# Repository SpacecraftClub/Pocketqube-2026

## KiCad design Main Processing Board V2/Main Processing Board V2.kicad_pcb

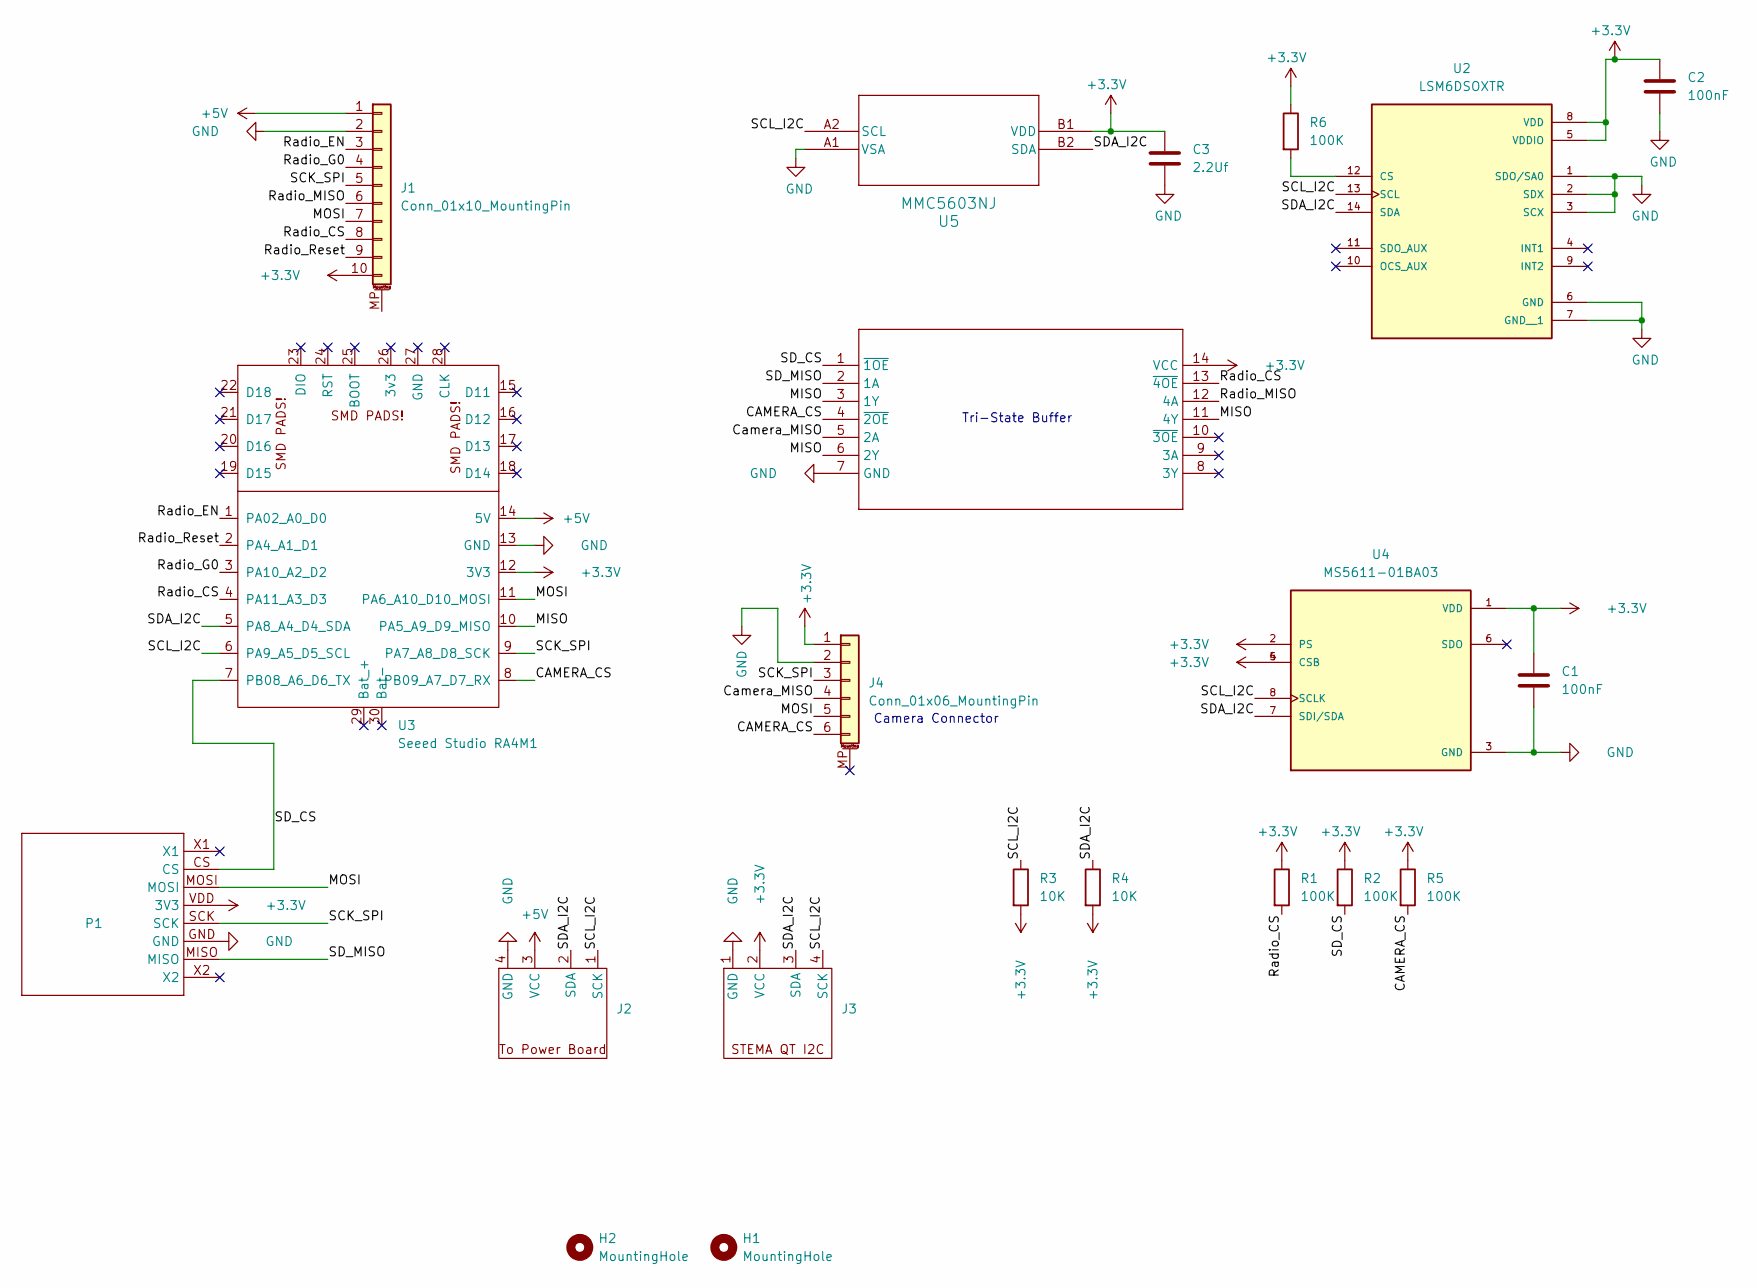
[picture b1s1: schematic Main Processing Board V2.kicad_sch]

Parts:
C1, C2: 100nF; C_1206_3216Metric_Pad1.33x1.80mm_HandSolder
C3: 2.2Uf; C_0603_1608Metric_Pad1.08x0.95mm_HandSolder
H1, H2: MountingHole; MountingHole_2.2mm_M2
J1: Conn_01x10_MountingPin; JST_SH_BM10B-SRSS-TB_1x10-1MP_P1.00mm_Vertical
J2, J3: JST_SH_BM04B-SRSS-TB_1x04-1MP_P1.00mm_Vertical
J4: Conn_01x06_MountingPin; JST_SH_BM06B-SRSS-TB_1x06-1MP_P1.00mm_Vertical
P1: SDREAD
R1, R2, R5, R6: 100K; R_0603_1608Metric_Pad0.98x0.95mm_HandSolder
R3, R4: 10K; R_0805_2012Metric_Pad1.20x1.40mm_HandSolder
U1: NS14
U2: LSM6DSOXTR; 14-VFLGA; PARTREV 3.0
U3: Seeed Studio RA4M1; XIAO-RA4M1-SMD
U4: MS5611-01BA03; SON125P500X300X100-8N; PARTREV 06/2017
U5: MMC5603NJ; WLP4_0P82X0P82_MEM

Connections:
+3.3V: C1.1, C2.1, C3.1, J1.10, J3.2 (VCC), J4.1, P1.VDD (3V3), R1.1, R2.1, R3.2, R4.2, R5.1, R6.1, U1.14 (VCC), U2.5 (VDDIO), U2.8 (VDD), U3.12 (3V3), U4.1 (VDD), U4.2 (PS), U4.4 (CSB), U4.5 (CSB), U5.B1 (VDD)
+5V: J1.1, J2.3 (VCC), U3.14 (5V)
/CAMERA_CS: J4.6, R5.2, U1.4 (~2OE), U3.8 (PB09_A7_D7_RX)
/Camera_MISO: J4.4, U1.5 (2A)
/MISO: U1.3 (1Y), U1.6 (2Y), U1.11 (4Y), U3.10 (PA5_A9_D9_MISO)
/MOSI: J1.7, J4.5, P1.MOSI, U3.11 (PA6_A10_D10_MOSI)
/Radio_CS: J1.8, R1.2, U1.13 (~4OE), U3.4 (PA11_A3_D3)
/Radio_EN: J1.3, U3.1 (PA02_A0_D0)
/Radio_G0: J1.4, U3.3 (PA10_A2_D2)
/Radio_MISO: J1.6, U1.12 (4A)
/Radio_Reset: J1.9, U3.2 (PA4_A1_D1)
/SCK_SPI: J1.5, J4.3, P1.SCK, U3.9 (PA7_A8_D8_SCK)
/SCL_I2C: J2.1 (SCK), J3.4 (SCK), R3.1, U2.13 (SCL), U3.6 (PA9_A5_D5_SCL), U4.8 (SCLK), U5.A2 (SCL)
/SDA_I2C: J2.2 (SDA), J3.3 (SDA), R4.1, U2.14 (SDA), U3.5 (PA8_A4_D4_SDA), U4.7 (SDI/SDA), U5.B2 (SDA)
/SD_CS: P1.CS, R2.2, U1.1 (~1OE), U3.7 (PB08_A6_D6_TX)
/SD_MISO: P1.MISO, U1.2 (1A)
GND: C1.2, C2.2, C3.2, J1.2, J2.4 (GND), J3.1 (GND), J4.2, P1.GND, U1.7 (GND), U2.1 (SDO/SA0), U2.2 (SDX), U2.3 (SCX), U2.6 (GND), U2.7 (GND__1), U3.13 (GND), U4.3 (GND), U5.A1 (VSA)
unnamed: R6.2, U2.12 (CS)

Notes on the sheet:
Camera Connector
Tri-State Buffer

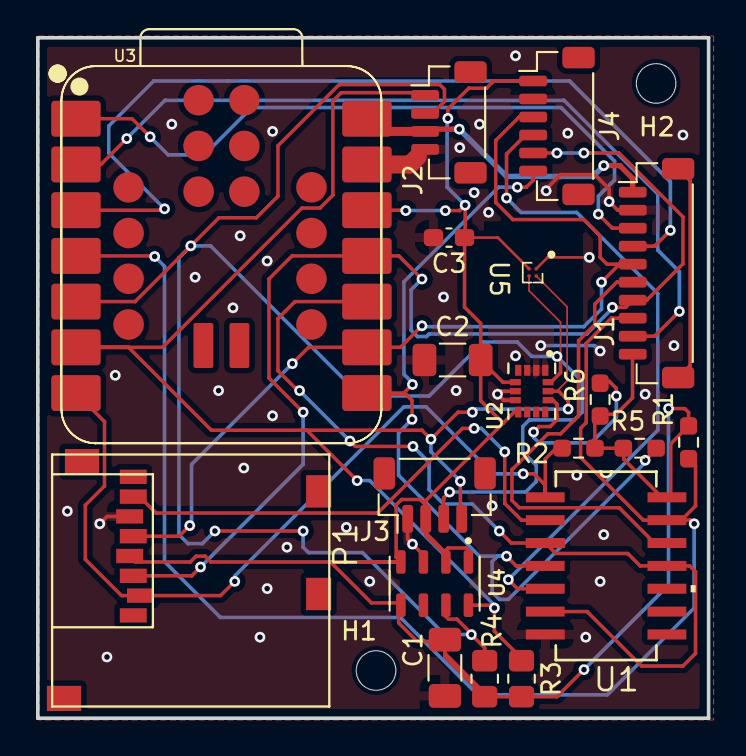
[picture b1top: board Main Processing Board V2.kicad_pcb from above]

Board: 2 copper layers, 37.3 x 37.8 mm, 21 parts (0 on the bottom side), 18 nets.

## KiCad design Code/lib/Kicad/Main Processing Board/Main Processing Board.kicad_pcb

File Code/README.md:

# PocketQube Flight Code

This firmware collects sensor data, logs it to the SD card, and transmits telemetry over LoRa radio.

## Viewing Data

There are three output paths:

1. Serial monitor
   Set `PRINT_SENSOR_CSV` to `true` in `src/main.cpp`. The firmware will print one CSV row per second at `9600` baud.

2. SD card logs
   Sensor data is written to CSV files by `src/sensor_logger.cpp`. Each row contains the current exported values for every sensor task.

3. Radio telemetry
   `src/radio.cpp` sends a binary packet containing a 2-byte sequence number followed by all exported sensor floats in task order.

## Sensor Task Order

Radio telemetry and CSV column order both follow the `sensorTasks[]` array in `src/taskHandles.cpp`.

Current task order:

1. `MS5611_Task`
2. `MMC5603_Task`
3. `LMSModule_Task`
4. `DS2782_BatteryMonitor_Task` when `POWER_MONITOR` is enabled

## Telemetry Field Order

### Base 12-float telemetry layout

If the battery monitor is not included in the radio payload, the 12 floats are:

1. `Pressure`
2. `Temp (MS5611)`
3. `x_mag`
4. `y_mag`
5. `z_mag`
6. `accel_x`
7. `accel_y`
8. `accel_z`
9. `gyro_x`
10. `gyro_y`
11. `gyro_z`
12. `temp_LMS`

Example:

`Telemetry: SEQ=9 Floats(12): 84966.555 23.303 913.164 1053.115 592.743 -0.002 0.120 1.024 -0.366 0.149 -0.549 20.222`

This maps to:

1. `84966.555` = `Pressure`
2. `23.303` = `Temp (MS5611)`
3. `913.164` = `x_mag`
4. `1053.115` = `y_mag`
5. `592.743` = `z_mag`
6. `-0.002` = `accel_x`
7. `0.120` = `accel_y`
8. `1.024` = `accel_z`
9. `-0.366` = `gyro_x`
10. `0.149` = `gyro_y`
11. `-0.549` = `gyro_z`
12. `20.222` = `temp_LMS`

### Battery monitor fields

When `POWER_MONITOR` is enabled, the DS2782 task adds these fields after `temp_LMS`:

13. `batt_voltage`
14. `batt_current`
15. `batt_power`
16. `batt_energy`
17. `batt_capacity`
18. `batt_soc`

## Likely Units

1. `Pressure`: Pa
2. `Temp (MS5611)`: C
3. `x_mag`, `y_mag`, `z_mag`: uT
4. `accel_x`, `accel_y`, `accel_z`: g
5. `gyro_x`, `gyro_y`, `gyro_z`: deg/s
6. `temp_LMS`: C
7. `batt_voltage`: V
8. `batt_current`: A
9. `batt_power`: W
10. `batt_energy`: J
11. `batt_capacity`: mAh
12. `batt_soc`: percent

## Important Radio Note

`src/radio.cpp` now computes the telemetry payload length from the enabled sensor tasks and checks it against `MAX_TELEMETRY_PACKET_LEN = 96`.

That is enough for the current telemetry set:

1. `2` bytes of sequence number
2. `18` floats = `72` bytes
3. Total `74` bytes

If more sensor fields are added later and the payload grows past `96` bytes, radio initialization will fail until the limit is increased.

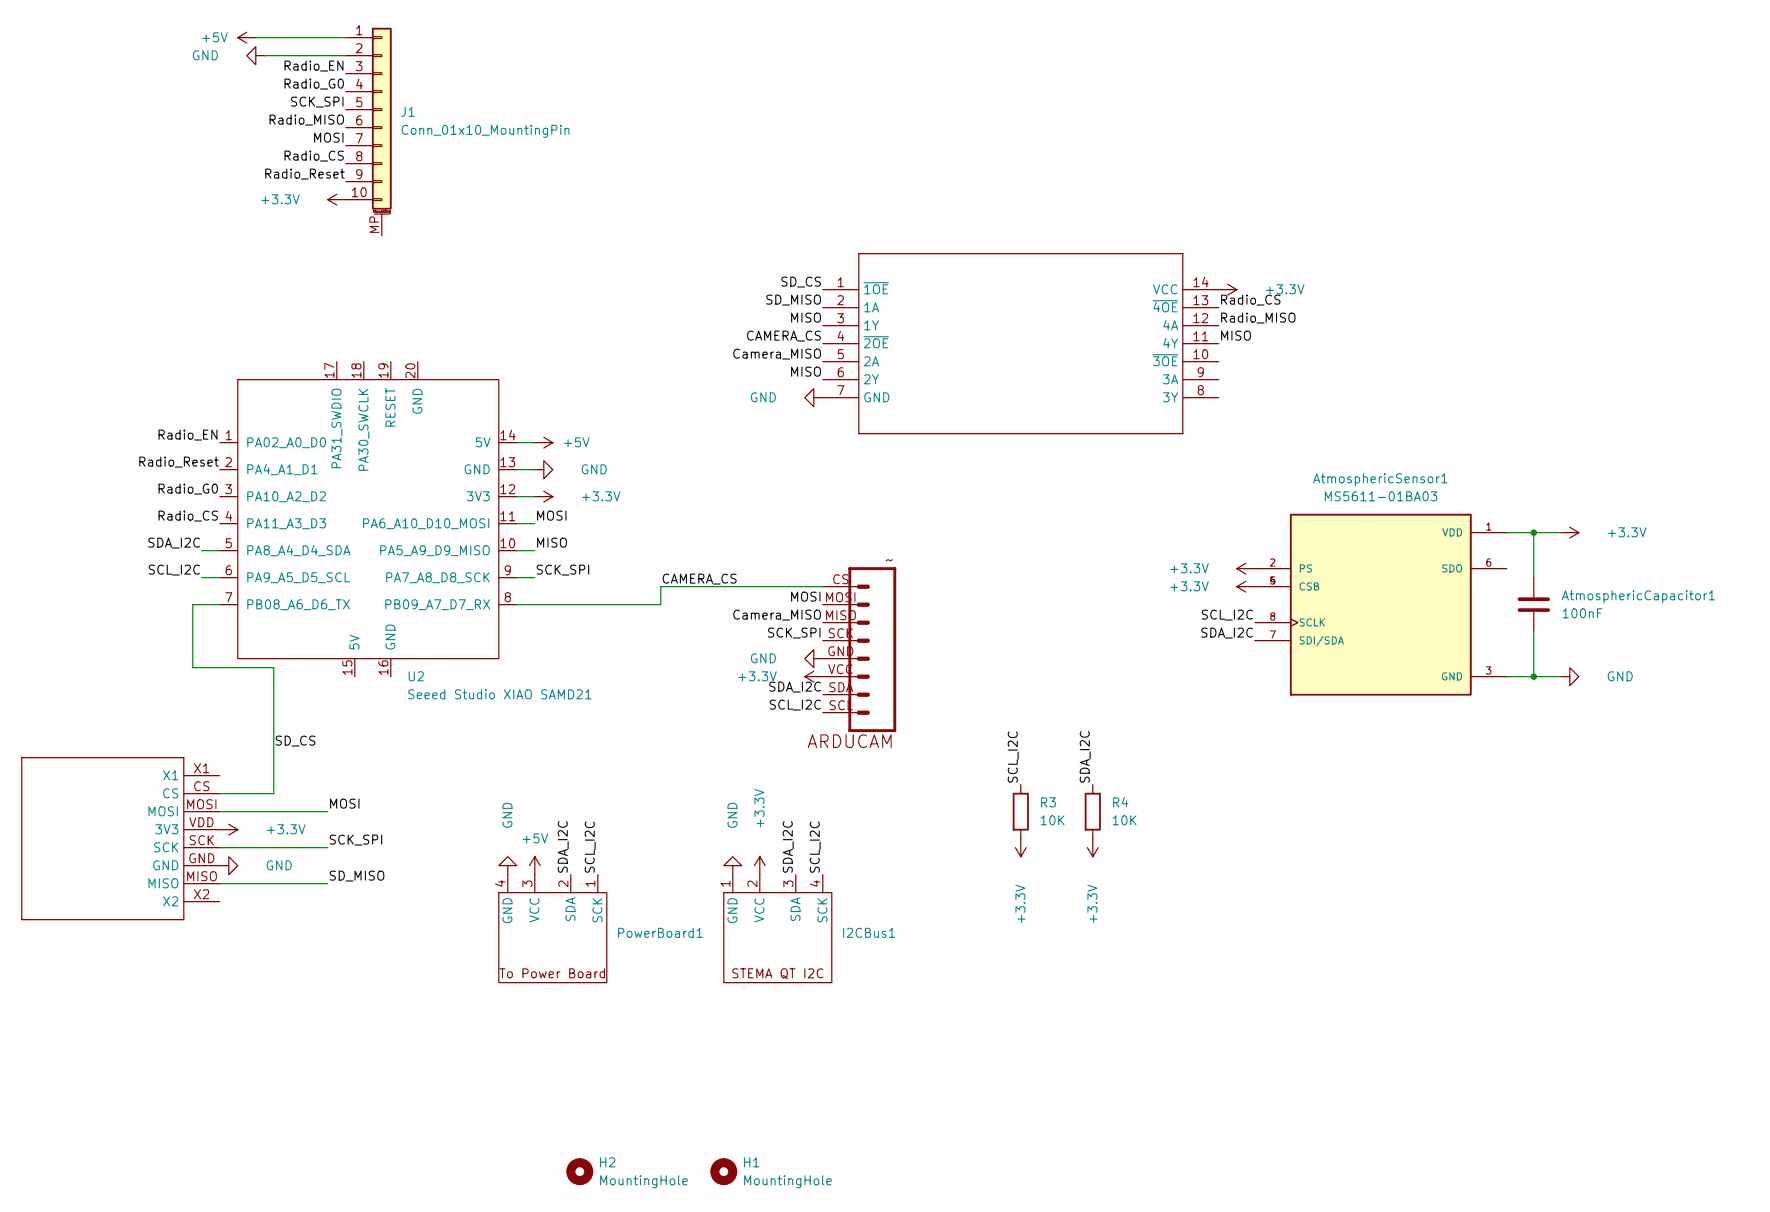
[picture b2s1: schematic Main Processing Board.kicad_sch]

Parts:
11111: SDREAD
12111: ARDUCAM_MINI
AtmosphericCapacitor1: 100nF; C_1206_3216Metric_Pad1.33x1.80mm_HandSolder
AtmosphericSensor1: MS5611-01BA03; SON125P500X300X100-8N; PARTREV 06/2017
H1, H2: MountingHole; MountingHole_2.2mm_M2
I2CBus1: JST_SH_BM04B-SRSS-TB_1x04-1MP_P1.00mm_Vertical
J1: Conn_01x10_MountingPin; JST_SH_BM10B-SRSS-TB_1x10-1MP_P1.00mm_Vertical
PowerBoard1: Molex_PicoBlade_53047-0410_1x04_P1.25mm_Vertical
R3, R4: 10K; R_0805_2012Metric_Pad1.20x1.40mm_HandSolder
U1: NS14
U2: Seeed Studio XIAO SAMD21; XIAO-SAMD21-SMD

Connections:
+3.3V: 11111.VDD (3V3), 12111.VCC, AtmosphericCapacitor1.1, AtmosphericSensor1.1 (VDD), AtmosphericSensor1.2 (PS), AtmosphericSensor1.4 (CSB), AtmosphericSensor1.5 (CSB), I2CBus1.2 (VCC), J1.10, R3.2, R4.2, U1.14 (VCC), U2.12 (3V3)
+5V: J1.1, PowerBoard1.3 (VCC), U2.14 (5V)
/CAMERA_CS: 12111.CS, U1.4 (~2OE), U2.8 (PB09_A7_D7_RX)
/Camera_MISO: 12111.MISO, U1.5 (2A)
/MISO: U1.3 (1Y), U1.6 (2Y), U1.11 (4Y), U2.10 (PA5_A9_D9_MISO)
/MOSI: 11111.MOSI, 12111.MOSI, J1.7, U2.11 (PA6_A10_D10_MOSI)
/Radio_CS: J1.8, U1.13 (~4OE), U2.4 (PA11_A3_D3)
/Radio_EN: J1.3, U2.1 (PA02_A0_D0)
/Radio_G0: J1.4, U2.3 (PA10_A2_D2)
/Radio_MISO: J1.6, U1.12 (4A)
/Radio_Reset: J1.9, U2.2 (PA4_A1_D1)
/SCK_SPI: 11111.SCK, 12111.SCK, J1.5, U2.9 (PA7_A8_D8_SCK)
/SCL_I2C: 12111.SCL, AtmosphericSensor1.8 (SCLK), I2CBus1.4 (SCK), PowerBoard1.1 (SCK), R3.1, U2.6 (PA9_A5_D5_SCL)
/SDA_I2C: 12111.SDA, AtmosphericSensor1.7 (SDI/SDA), I2CBus1.3 (SDA), PowerBoard1.2 (SDA), R4.1, U2.5 (PA8_A4_D4_SDA)
/SD_CS: 11111.CS, U1.1 (~1OE), U2.7 (PB08_A6_D6_TX)
/SD_MISO: 11111.MISO, U1.2 (1A)
GND: 11111.GND, 12111.GND, AtmosphericCapacitor1.2, AtmosphericSensor1.3 (GND), I2CBus1.1 (GND), J1.2, PowerBoard1.4 (GND), U1.7 (GND), U2.13 (GND)

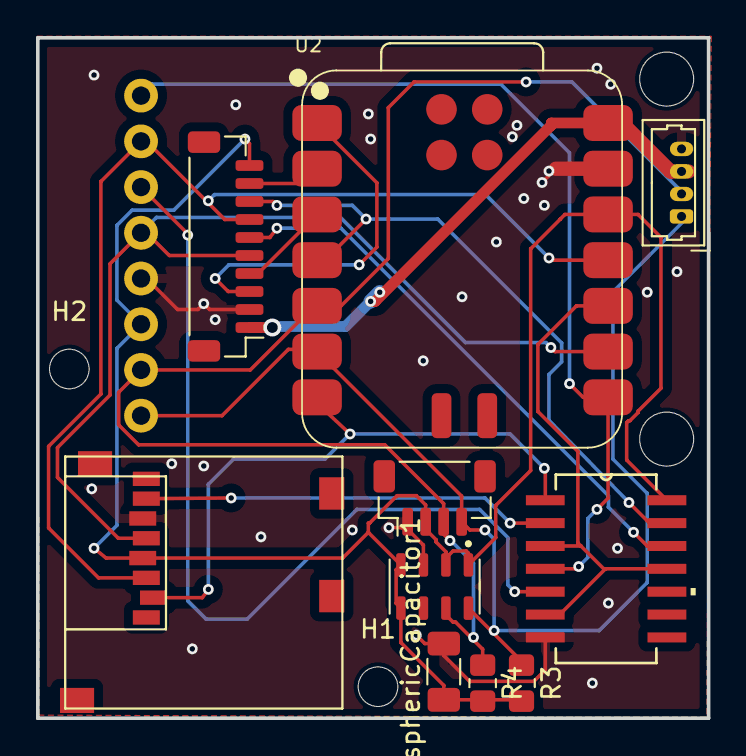
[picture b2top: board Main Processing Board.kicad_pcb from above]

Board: 2 copper layers, 37.3 x 37.8 mm, 13 parts (1 on the bottom side), 17 nets.

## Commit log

2025-09-24 started routing
    added ground plane
2025-09-24 more routing
    I worked on the routing some more, focusing mostly on the bottom right corner. I still need to change the thickness of the connections I made to 0.5
2025-10-01 added altium files
2025-10-01 added more altium files
2025-10-01 more routing
    I did some more routing. Will likely have to redo part of it, as I'm getting stuck
2025-10-07 more routing
    Did as much as I could but got stuck so will need to redo some parts.
2025-10-08 Finished PCB Routing
    There were some merge conflicts, so if something seems off, then it probably is.
2025-10-15 edited connection widths
2025-10-29 added BOM work
2025-11-05 updated 3d model
2025-11-26 Updated code
    Code now works with current hardware
2026-01-28 Added Test code for camera
2026-01-28 Updated code to verify UHD camera
2026-01-29 started creating stats.cpp
    - added unit tests as well
2026-02-02 Finished Preliminary Stats Library
    - Now you can calculate the mean of a dataset (without outliers)
    - Added Unit Tests to verify functionality of the library
2026-02-03 Updated Scheduler
    Set ground work so that we can begin making the new sensor platform
    - New task based scheduler for modularity
    - Cleaned code to make it more readable & configurable
2026-02-03 Added some stats errors prevention
2026-02-11 MMC5603 sensor code
    Wrote code for MMC5603 sensor. It compiles
2026-02-18 Camera now works and is more stable
2026-02-25 LMS Module files
    Wrote .h and .cpp files for the LMS Module functions
2026-03-04 Added sensor logger header file
2026-03-04 Created sensor_logger.cpp
    Implemented initializer
2026-03-11 Resolved Stats Error
2026-03-11 adjusted prints to only print when debugging
2026-03-11 Updated Stats Tests
    Now it tests calculated means of raw data.
2026-03-25 Updated sensor_logger.cpp
2026-03-26 working logging code
2026-04-23 radio code
2026-04-24 updated radio parameters
2026-04-25 updated radio and power monitor code
2026-04-25 removed power monitor code
2026-04-28 Added 3d Models
    + print profiles
